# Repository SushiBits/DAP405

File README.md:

# DAP405 Mini Debug Probe for ARM

An advanced USB 2.0 Hi-Speed CMSIS-DAP debug probe for ARM Cortex processors.

## Introduction

DAP405 is a CMSIS-DAP compatible USB JTAG debug adapter for ARM Cortex-A and
Cortex-M processors, based on the STM32F405RG microcontroller.

This project is an evolution of[my DAP42 project](https://github.com/SushiBits/DAP42).

## License and contact

This is open source hardware under [3-clause BSD license](LICENSE.md).

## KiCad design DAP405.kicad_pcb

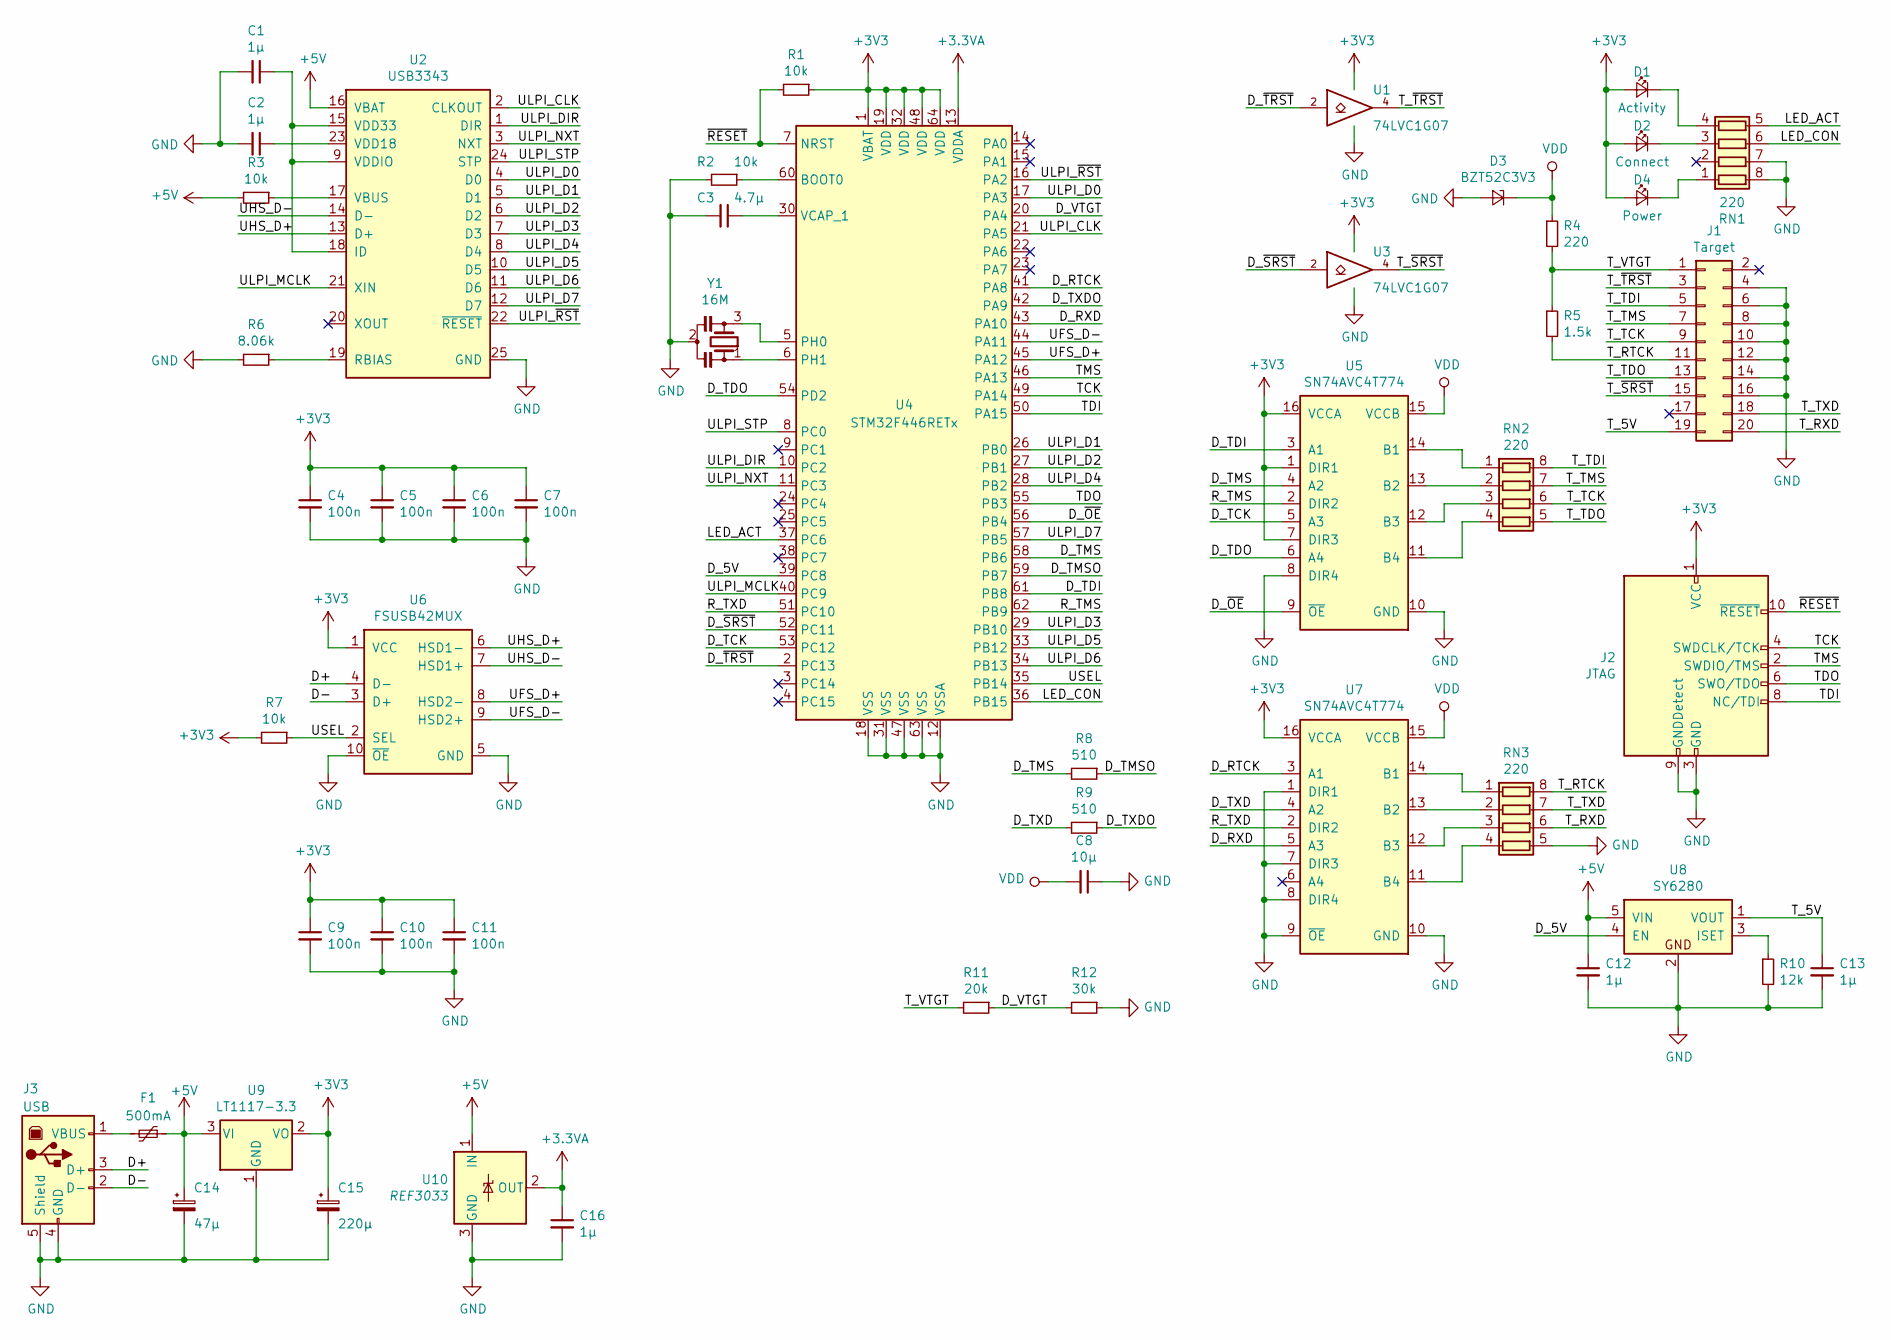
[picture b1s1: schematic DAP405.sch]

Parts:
C1, C2, C12, C13, C16: 1µ; C_0603_1608Metric_Pad1.05x0.95mm_HandSolder
C3: 4.7µ; C_0603_1608Metric_Pad1.05x0.95mm_HandSolder
C4, C5, C6, C7, C9, C10, C11: 100n; C_0603_1608Metric_Pad1.05x0.95mm_HandSolder
C8: 10µ; C_0805_2012Metric_Pad1.15x1.40mm_HandSolder
C14: 47µ; CP_EIA-3528-21_Kemet-B_Pad1.50x2.35mm_HandSolder
C15: 220µ; CP_EIA-3528-21_Kemet-B_Pad1.50x2.35mm_HandSolder
D1: Activity; LED_D3.0mm
D2: Connect; LED_D3.0mm
D3: BZT52C3V3; D_SOD-123
D4: Power; LED_D3.0mm
F1: 500mA; Fuse_1812_4532Metric_Pad1.30x3.40mm_HandSolder
J1: Target; IDC-Header_2x10_P2.54mm_Horizontal
J2: JTAG; PinHeader_2x05_P1.27mm_Vertical_SMD
J3: USB; USB_B_OST_USB-B1HSxx_Horizontal
R1, R2, R3, R7: 10k; R_0603_1608Metric_Pad1.05x0.95mm_HandSolder
R4: 220; R_0603_1608Metric_Pad1.05x0.95mm_HandSolder
R5: 1.5k; R_0603_1608Metric_Pad1.05x0.95mm_HandSolder
R6: 8.06k; R_0603_1608Metric_Pad1.05x0.95mm_HandSolder
R8, R9: 510; R_0603_1608Metric_Pad1.05x0.95mm_HandSolder
R10: 12k; R_0603_1608Metric_Pad1.05x0.95mm_HandSolder
R11: 20k; R_0603_1608Metric_Pad1.05x0.95mm_HandSolder
R12: 30k; R_0603_1608Metric_Pad1.05x0.95mm_HandSolder
RN1, RN2, RN3: 220; R_Array_Convex_4x0603
U1, U3: 74LVC1G07; SOT-23-5
U2: USB3343; QFN-24-1EP_4x4mm_P0.5mm_EP2.6x2.6mm
U4: STM32F446RETx; LQFP-64_10x10mm_P0.5mm
U5, U7: SN74AVC4T774; TSSOP-16_4.4x5mm_P0.65mm
U6: FSUSB42MUX; MSOP-10_3x3mm_P0.5mm
U8: SY6280; SOT-23-5
U9: LT1117-3.3; SOT-89-3
U10: REF3033; SOT-23
Y1: 16M; Resonator_SMD_muRata_CSTxExxV-3Pin_3.0x1.1mm

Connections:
+3.3VA: C16.1, U4.13 (VDDA), U10.2 (OUT)
+3V3: C4.1, C5.1, C6.1, C7.1, C9.1, C10.1, C11.1, C15.1, D1.2 (A), D2.2 (A), D4.2 (A), J2.1 (VCC), R1.1, R7.2, U1.5 (VCC), U3.5 (VCC), U4.1 (VBAT), U4.19 (VDD), U4.32 (VDD), U4.48 (VDD), U4.64 (VDD), U5.1 (DIR1), U5.7 (DIR3), U5.16 (VCCA), U6.1 (VCC), U7.16 (VCCA), U9.2 (VO)
+5V: C12.1, C14.1, F1.1, R3.2, U2.16 (VBAT), U8.5 (VIN), U9.3 (VI), U10.1 (IN)
/D+: J3.3 (D+), U6.4 (D-)
/D-: J3.2 (D-), U6.3 (D+)
/D_5V: U4.39 (PC8), U8.4 (EN)
/D_RTCK: U4.41 (PA8), U7.3 (A1)
/D_RXD: U4.43 (PA10), U7.5 (A3)
/D_TCK: U4.53 (PC12), U5.5 (A3)
/D_TDI: U4.61 (PB8), U5.3 (A1)
/D_TDO: U4.54 (PD2), U5.6 (A4)
/D_TMS: R8.2, U4.58 (PB6), U5.4 (A2)
/D_TMSO: R8.1, U4.59 (PB7)
/D_TXD: R9.2, U7.4 (A2)
/D_TXDO: R9.1, U4.42 (PA9)
/D_VTGT: R11.1, R12.2, U4.20 (PA4)
/D_~OE: U4.56 (PB4), U5.9 (~OE)
/D_~SRST: U3.2, U4.52 (PC11)
/D_~TRST: U1.2, U4.2 (PC13)
/LED_ACT: RN1.5 (R4.2), U4.37 (PC6)
/LED_CON: RN1.6 (R3.2), U4.36 (PB15)
/R_TMS: U4.62 (PB9), U5.2 (DIR2)
/R_TXD: U4.51 (PC10), U7.2 (DIR2)
/TCK: J2.4 (SWDCLK/TCK), U4.49 (PA14)
/TDI: J2.8 (NC/TDI), U4.50 (PA15)
/TDO: J2.6 (SWO/TDO), U4.55 (PB3)
/TMS: J2.2 (SWDIO/TMS), U4.46 (PA13)
/T_5V: C13.1, J1.19, U8.1 (VOUT)
/T_RTCK: J1.11, R5.2, RN3.8 (R1.2)
/T_RXD: J1.20, RN3.6 (R3.2)
/T_TCK: J1.9, RN2.6 (R3.2)
/T_TDI: J1.5, RN2.8 (R1.2)
/T_TDO: J1.13, RN2.5 (R4.2)
/T_TMS: J1.7, RN2.7 (R2.2)
/T_TXD: J1.18, RN3.7 (R2.2)
/T_VTGT: J1.1, R4.2, R5.1, R11.2
/T_~SRST: J1.15, U3.4
/T_~TRST: J1.3, U1.4
/UFS_D+: U4.45 (PA12), U6.8 (HSD2-)
/UFS_D-: U4.44 (PA11), U6.9 (HSD2+)
/UHS_D+: U2.13 (D+), U6.6 (HSD1-)
/UHS_D-: U2.14 (D-), U6.7 (HSD1+)
/ULPI_CLK: U2.2 (CLKOUT), U4.21 (PA5)
/ULPI_D0: U2.4 (D0), U4.17 (PA3)
/ULPI_D1: U2.5 (D1), U4.26 (PB0)
/ULPI_D2: U2.6 (D2), U4.27 (PB1)
/ULPI_D3: U2.7 (D3), U4.29 (PB10)
/ULPI_D4: U2.8 (D4), U4.28 (PB2)
/ULPI_D5: U2.10 (D5), U4.33 (PB12)
/ULPI_D6: U2.11 (D6), U4.34 (PB13)
/ULPI_D7: U2.12 (D7), U4.57 (PB5)
/ULPI_DIR: U2.1 (DIR), U4.10 (PC2)
/ULPI_MCLK: U2.21 (XIN), U4.40 (PC9)
/ULPI_NXT: U2.3 (NXT), U4.11 (PC3)
/ULPI_STP: U2.24 (STP), U4.8 (PC0)
/ULPI_~RST: U2.22 (~RESET), U4.16 (PA2)
/USEL: R7.1, U4.35 (PB14), U6.2 (SEL)
/~RESET: J2.10 (~RESET~), R1.2, U4.7 (NRST)
GND: C1.2, C2.2, C3.2, C4.2, C5.2, C6.2, C7.2, C8.1, C9.2, C10.2, C11.2, C12.2, C13.2, C14.2, C15.2, C16.2, D3.2 (A), J1.4, J1.6, J1.8, J1.10, J1.12, J1.14, J1.16, J2.3 (GND), J2.5 (GND), J2.9 (GNDDetect), J3.4 (GND), J3.5 (Shield), R2.2, R6.2, R10.2, R12.1, RN1.7 (R2.2), RN1.8 (R1.2), RN3.5 (R4.2), U1.3 (GND), U2.25 (GND), U3.3 (GND), U4.12 (VSSA), U4.18 (VSS), U4.31 (VSS), U4.47 (VSS), U4.63 (VSS), U5.8 (DIR4), U5.10 (GND), U6.5 (GND), U6.10 (~OE), U7.1 (DIR1), U7.7 (DIR3), U7.8 (DIR4), U7.9 (~OE), U7.10 (GND), U8.2, U9.1 (GND), U10.3 (GND), Y1.2
unnamed: C1.1, U2.9 (VDDIO), U2.15 (VDD33), U2.18 (ID)
unnamed: C2.1, U2.23 (VDD18)
unnamed: C3.1, U4.30 (VCAP_1)
unnamed: D1.1 (K), RN1.4 (R4.1)
unnamed: D2.1 (K), RN1.3 (R3.1)
unnamed: D4.1 (K), RN1.1 (R1.1)
unnamed: F1.2, J3.1 (VBUS)
unnamed: R2.1, U4.60 (BOOT0)
unnamed: R3.1, U2.17 (VBUS)
unnamed: R6.1, U2.19 (RBIAS)
unnamed: R10.1, U8.3 (ISET)
unnamed: RN2.1 (R1.1), U5.14 (B1)
unnamed: RN2.2 (R2.1), U5.13 (B2)
unnamed: RN2.3 (R3.1), U5.12 (B3)
unnamed: RN2.4 (R4.1), U5.11 (B4)
unnamed: RN3.1 (R1.1), U7.14 (B1)
unnamed: RN3.2 (R2.1), U7.13 (B2)
unnamed: RN3.3 (R3.1), U7.12 (B3)
unnamed: RN3.4 (R4.1), U7.11 (B4)
unnamed: U4.5 (PH0), Y1.3
unnamed: U4.6 (PH1), Y1.1
VDD: C8.2, D3.1 (K), R4.1, U5.15 (VCCB), U7.15 (VCCB)

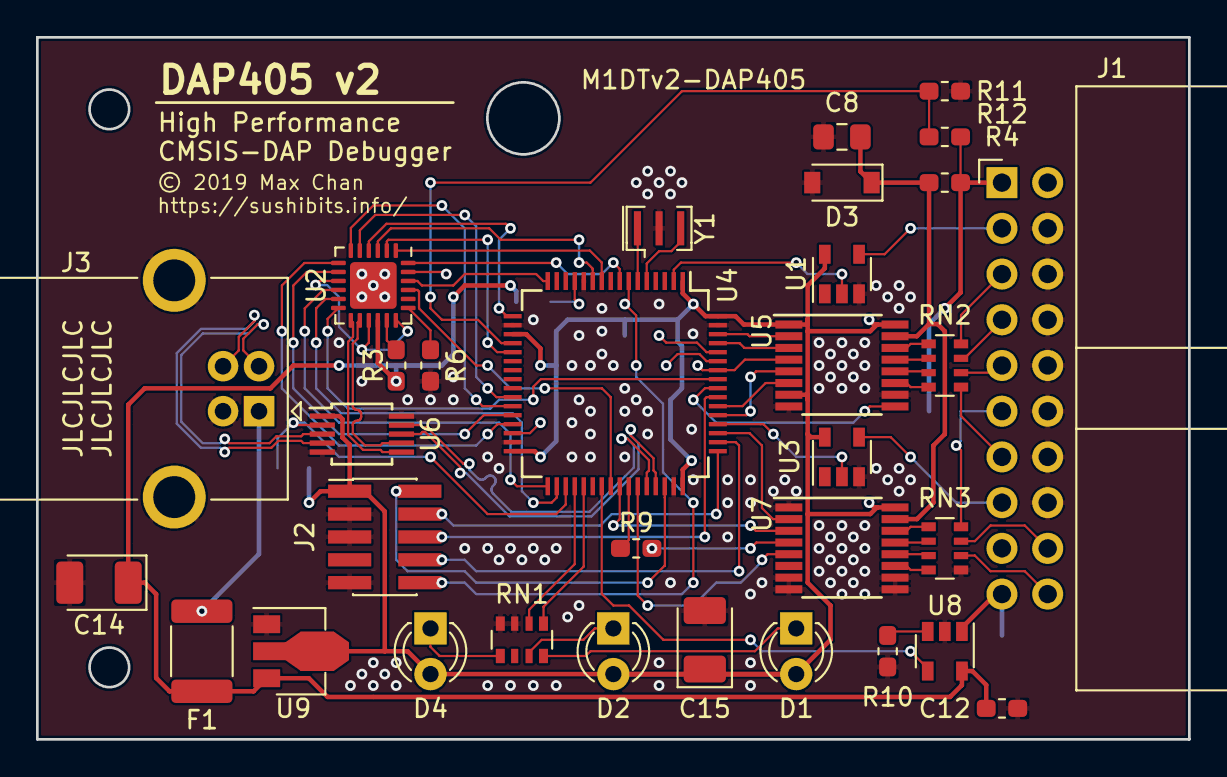
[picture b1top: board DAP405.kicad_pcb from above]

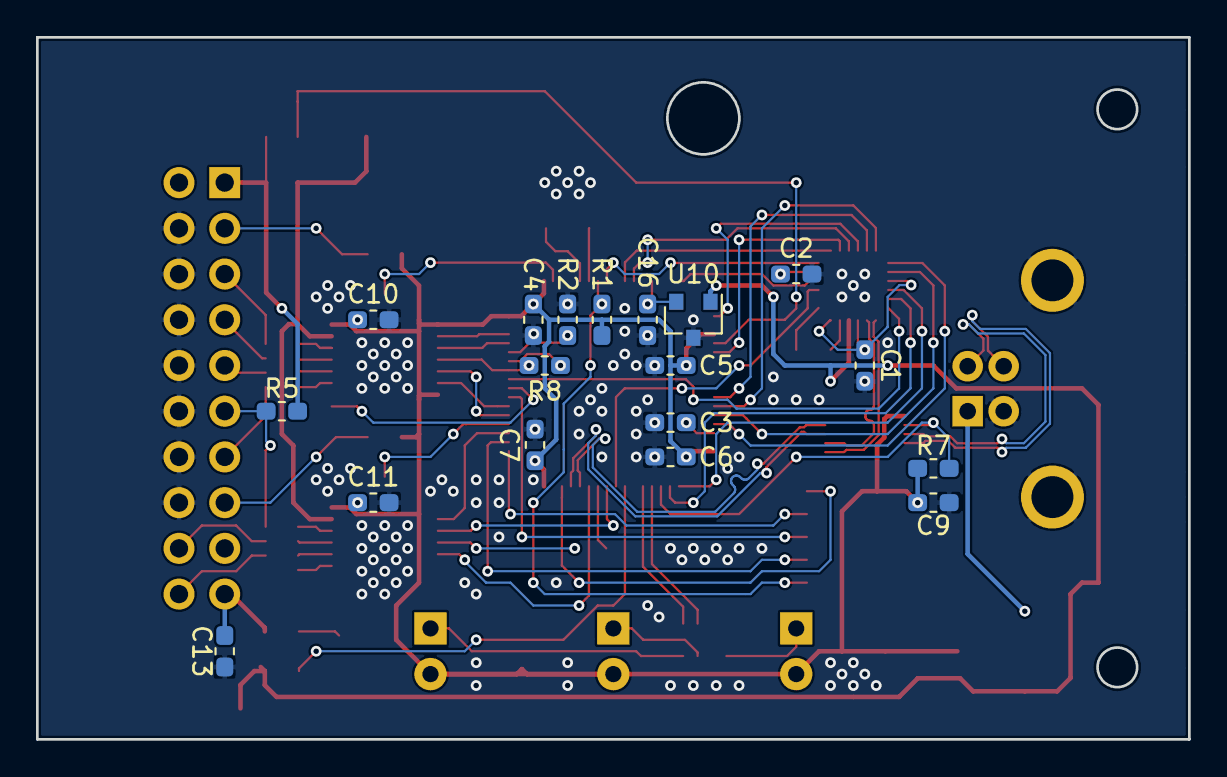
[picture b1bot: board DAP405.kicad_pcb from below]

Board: 2 copper layers, 64.0 x 39.0 mm, 50 parts (18 on the bottom side), 81 nets.

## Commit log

2019-07-26 Code dump
2019-07-26 Fixing the ULPI interface.
2019-09-01 STM32F446 version

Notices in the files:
DAP405.kicad_pcb:
© 2019 Max Chan
